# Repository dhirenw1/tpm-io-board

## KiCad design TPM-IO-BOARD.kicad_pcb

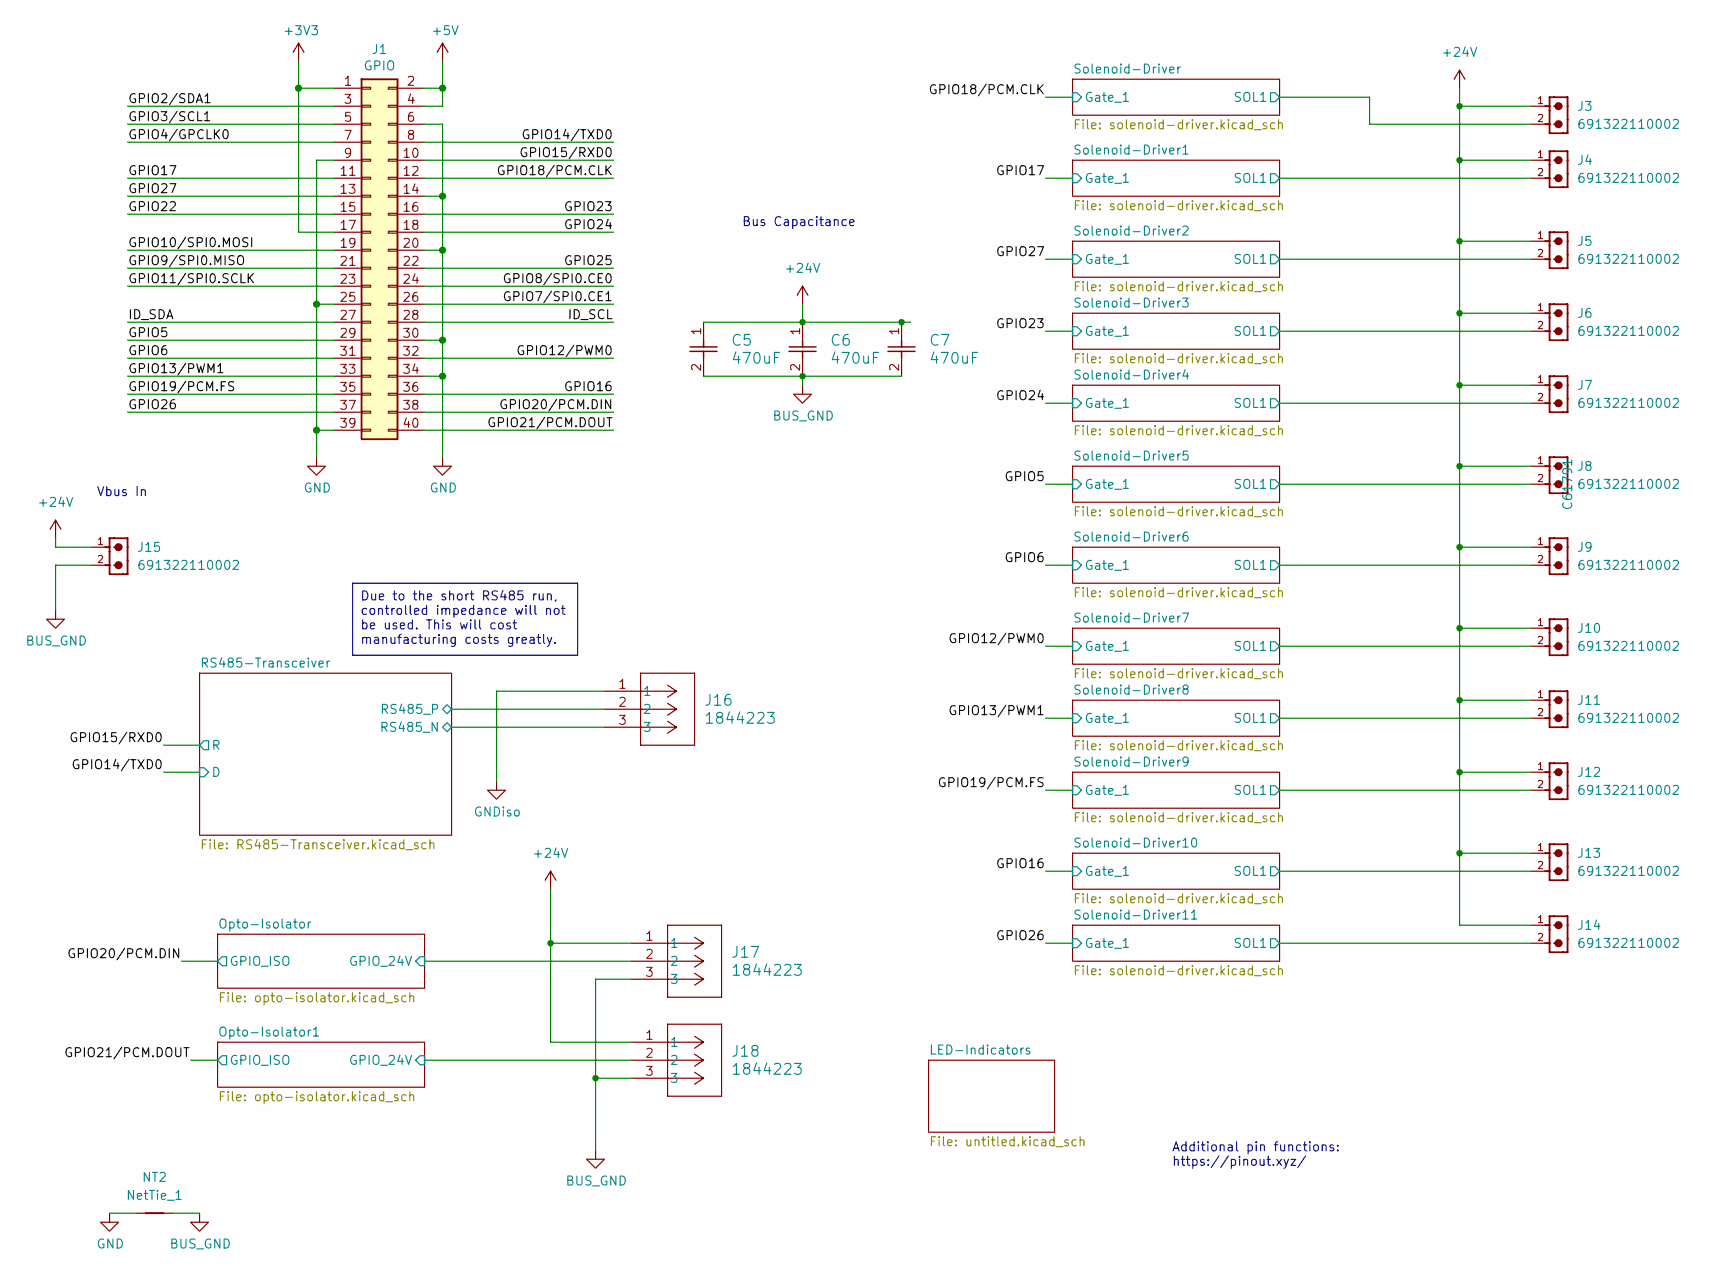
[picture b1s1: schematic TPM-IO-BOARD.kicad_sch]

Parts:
C5, C6, C7: 470uF; CAP_YX_10X16_RUB; LCSC C338196
J1: GPIO; PinSocket_2x20_P2.54mm_Vertical; LCSC C35165
J3, J4, J5, J6, J7, J8, J9, J10, J11, J12, J13, J14, J15: 691322110002; PART-NUMBER 691322110002; LCSC C61791
J16, J17, J18: 1844223; CONN_1844223_PXC; LCSC C5244104
NT2: NetTie_1; NetTie-2_SMD_Pad0.5mm

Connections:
+3V3: J1.1, J1.17; also elsewhere on the board
+5V: J1.2, J1.4; also elsewhere on the board
+24V: C5.1, C6.1, C7.1, J3.1, J4.1, J5.1, J6.1, J7.1, J8.1, J9.1, J10.1, J11.1, J12.1, J13.1, J14.1, J15.1, J17.1, J18.1; also elsewhere on the board
/GPIO2/SDA1: J1.3
/GPIO3/SCL1: J1.5
/GPIO4/GPCLK0: J1.7
/GPIO5: J1.29; also elsewhere on the board
/GPIO6: J1.31; also elsewhere on the board
/GPIO7/SPI0.CE1: J1.26
/GPIO8/SPI0.CE0: J1.24
/GPIO9/SPI0.MISO: J1.21
/GPIO10/SPI0.MOSI: J1.19
/GPIO11/SPI0.SCLK: J1.23
/GPIO12/PWM0: J1.32; also elsewhere on the board
/GPIO13/PWM1: J1.33; also elsewhere on the board
/GPIO14/TXD0: J1.8; also elsewhere on the board
/GPIO15/RXD0: J1.10; also elsewhere on the board
/GPIO16: J1.36; also elsewhere on the board
/GPIO17: J1.11; also elsewhere on the board
/GPIO18/PCM.CLK: J1.12; also elsewhere on the board
/GPIO19/PCM.FS: J1.35; also elsewhere on the board
/GPIO20/PCM.DIN: J1.38; also elsewhere on the board
/GPIO21/PCM.DOUT: J1.40; also elsewhere on the board
/GPIO22: J1.15
/GPIO23: J1.16; also elsewhere on the board
/GPIO24: J1.18; also elsewhere on the board
/GPIO25: J1.22
/GPIO26: J1.37; also elsewhere on the board
/GPIO27: J1.13; also elsewhere on the board
/ID_SCL: J1.28
/ID_SDA: J1.27
/Opto-Isolator1/GPIO_24V: J18.2; also elsewhere on the board
/Opto-Isolator/GPIO_24V: J17.2; also elsewhere on the board
/RS485-Transceiver/RS485_N: J16.3; also elsewhere on the board
/RS485-Transceiver/RS485_P: J16.2; also elsewhere on the board
/Solenoid-Driver1/SOL1: J4.2; also elsewhere on the board
/Solenoid-Driver2/SOL1: J5.2; also elsewhere on the board
/Solenoid-Driver3/SOL1: J6.2; also elsewhere on the board
/Solenoid-Driver4/SOL1: J7.2; also elsewhere on the board
/Solenoid-Driver5/SOL1: J8.2; also elsewhere on the board
/Solenoid-Driver6/SOL1: J9.2; also elsewhere on the board
/Solenoid-Driver7/SOL1: J10.2; also elsewhere on the board
/Solenoid-Driver8/SOL1: J11.2; also elsewhere on the board
/Solenoid-Driver9/SOL1: J12.2; also elsewhere on the board
/Solenoid-Driver10/SOL1: J13.2; also elsewhere on the board
/Solenoid-Driver11/SOL1: J14.2; also elsewhere on the board
/Solenoid-Driver/SOL1: J3.2; also elsewhere on the board
BUS_GND: C5.2, C6.2, C7.2, J15.2, J17.3, J18.3, NT2.2; also elsewhere on the board
GND: J1.6, J1.9, J1.14, J1.20, J1.25, J1.30, J1.34, J1.39, NT2.1; also elsewhere on the board
GNDiso: J16.1; also elsewhere on the board

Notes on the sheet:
Due to the short RS485 run, controlled impedance will not be used. This will cost manufacturing costs greatly.
Additional pin functions: https://pinout.xyz/
Bus Capacitance
Vbus In

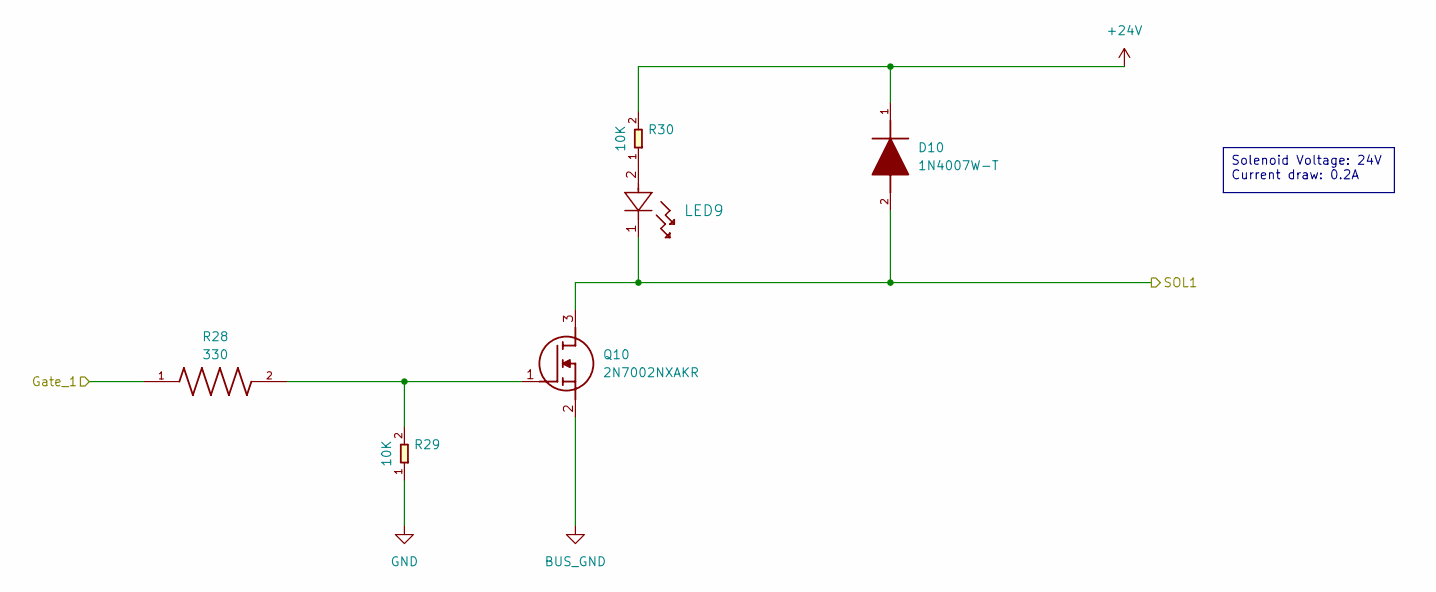
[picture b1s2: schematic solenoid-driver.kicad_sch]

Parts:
D10: 1N4007W-T; SODFL3818X130N; Mouser_Part_Number 583-1N4007W-T
LED9: 5988A10107F; LED_5988A10107F_DIA; LCSC C264407
Q10: 2N7002NXAKR; SOT95P230X110-3N; Mouser Part Number 771-2N7002NXAKR
R28: 330; RESC1005X40N; LCSC C517531
R29, R30: SMD-RES-10K-5_-1__0402_; R0402; MPN RC0402JR-0710KL; LCSC C319934

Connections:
+24V: D10.1, R30.2; also elsewhere on the board
/GPIO19/PCM.FS: R28.1; also elsewhere on the board
/Solenoid-Driver9/SOL1: D10.2, LED9.1, Q10.3 (D); also elsewhere on the board
BUS_GND: Q10.2 (S); also elsewhere on the board
GND: R29.1; also elsewhere on the board
unnamed: LED9.2, R30.1
unnamed: Q10.1 (G), R28.2, R29.2

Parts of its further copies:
D1, D2, D3, D4, D5, D6, D7, D8, D9, D11, D12: 1N4007W-T; SODFL3818X130N; Mouser_Part_Number 583-1N4007W-T
LED1, LED2, LED3, LED4, LED5, LED6, LED7, LED8, LED10, LED11, LED13: 5988A10107F; LED_5988A10107F_DIA; LCSC C264407
Q1, Q2, Q3, Q4, Q5, Q6, Q7, Q8, Q9, Q11, Q12: 2N7002NXAKR; SOT95P230X110-3N; Mouser Part Number 771-2N7002NXAKR
R2, R3, R7, R10, R13, R16, R19, R22, R25, R31, R36: 330; RESC1005X40N; LCSC C517531
R4, R5, R6, R8, R9, R11, R12, R14, R15, R17, R18, R20, R21, R23, R24, R26, R27, R32, R33, R37, R38, R39: SMD-RES-10K-5_-1__0402_; R0402; MPN RC0402JR-0710KL; LCSC C319934

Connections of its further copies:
+24V: D1.1, D2.1, D3.1, D4.1, D5.1, D6.1, D7.1, D8.1, D9.1, D11.1, D12.1, R5.2, R9.2, R12.2, R15.2, R18.2, R21.2, R24.2, R27.2, R33.2, R38.2, R39.2; also elsewhere on the board
/GPIO5: R16.1; also elsewhere on the board
/GPIO6: R19.1; also elsewhere on the board
/GPIO12/PWM0: R22.1; also elsewhere on the board
/GPIO13/PWM1: R25.1; also elsewhere on the board
/GPIO16: R31.1; also elsewhere on the board
/GPIO17: R3.1; also elsewhere on the board
/GPIO18/PCM.CLK: R2.1; also elsewhere on the board
/GPIO23: R10.1; also elsewhere on the board
/GPIO24: R13.1; also elsewhere on the board
/GPIO26: R36.1; also elsewhere on the board
/GPIO27: R7.1; also elsewhere on the board
/Solenoid-Driver1/SOL1: D2.2, LED1.1, Q2.3 (D); also elsewhere on the board
/Solenoid-Driver2/SOL1: D3.2, LED2.1, Q3.3 (D); also elsewhere on the board
/Solenoid-Driver3/SOL1: D4.2, LED3.1, Q4.3 (D); also elsewhere on the board
/Solenoid-Driver4/SOL1: D5.2, LED4.1, Q5.3 (D); also elsewhere on the board
/Solenoid-Driver5/SOL1: D6.2, LED5.1, Q6.3 (D); also elsewhere on the board
/Solenoid-Driver6/SOL1: D7.2, LED6.1, Q7.3 (D); also elsewhere on the board
/Solenoid-Driver7/SOL1: D8.2, LED7.1, Q8.3 (D); also elsewhere on the board
/Solenoid-Driver8/SOL1: D9.2, LED8.1, Q9.3 (D); also elsewhere on the board
/Solenoid-Driver10/SOL1: D11.2, LED10.1, Q11.3 (D); also elsewhere on the board
/Solenoid-Driver11/SOL1: D12.2, LED11.1, Q12.3 (D); also elsewhere on the board
/Solenoid-Driver/SOL1: D1.2, LED13.1, Q1.3 (D); also elsewhere on the board
BUS_GND: Q1.2 (S), Q2.2 (S), Q3.2 (S), Q4.2 (S), Q5.2 (S), Q6.2 (S), Q7.2 (S), Q8.2 (S), Q9.2 (S), Q11.2 (S), Q12.2 (S); also elsewhere on the board
GND: R4.1, R6.1, R8.1, R11.1, R14.1, R17.1, R20.1, R23.1, R26.1, R32.1, R37.1; also elsewhere on the board
unnamed: LED1.2, R5.1
unnamed: LED2.2, R9.1
unnamed: LED3.2, R12.1
unnamed: LED4.2, R15.1
unnamed: LED5.2, R18.1
unnamed: LED6.2, R21.1
unnamed: LED7.2, R24.1
unnamed: LED8.2, R27.1
unnamed: LED10.2, R33.1
unnamed: LED11.2, R39.1
unnamed: LED13.2, R38.1
unnamed: Q1.1 (G), R2.2, R6.2
unnamed: Q2.1 (G), R3.2, R4.2
unnamed: Q3.1 (G), R7.2, R8.2
unnamed: Q4.1 (G), R10.2, R11.2
unnamed: Q5.1 (G), R13.2, R14.2
unnamed: Q6.1 (G), R16.2, R17.2
unnamed: Q7.1 (G), R19.2, R20.2
unnamed: Q8.1 (G), R22.2, R23.2
unnamed: Q9.1 (G), R25.2, R26.2
unnamed: Q11.1 (G), R31.2, R32.2
unnamed: Q12.1 (G), R36.2, R37.2

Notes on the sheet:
Solenoid Voltage: 24V Current draw: 0.2A

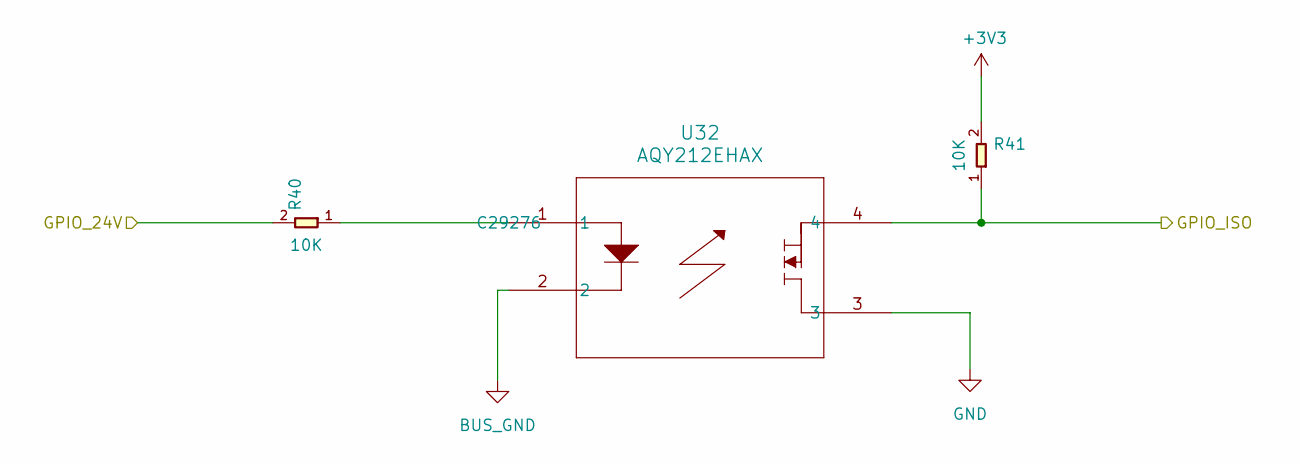
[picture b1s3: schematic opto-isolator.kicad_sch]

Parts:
R40, R41: SMD-RES-10K-5_-1__0402_; R0402; MPN RC0402JR-0710KL; LCSC C319934
U32: AQY212EHAX; RELAY_AQY_SO4_EH_PAN; LCSC C29276

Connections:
+3V3: R41.2; also elsewhere on the board
/GPIO20/PCM.DIN: R41.1, U32.4; also elsewhere on the board
/Opto-Isolator/GPIO_24V: R40.2; also elsewhere on the board
BUS_GND: U32.2; also elsewhere on the board
GND: U32.3; also elsewhere on the board
unnamed: R40.1, U32.1

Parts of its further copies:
R34, R35: SMD-RES-10K-5_-1__0402_; R0402; MPN RC0402JR-0710KL; LCSC C319934
U7: AQY212EHAX; RELAY_AQY_SO4_EH_PAN; LCSC C29276

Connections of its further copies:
+3V3: R35.2; also elsewhere on the board
/GPIO21/PCM.DOUT: R35.1, U7.4; also elsewhere on the board
/Opto-Isolator1/GPIO_24V: R34.2; also elsewhere on the board
BUS_GND: U7.2; also elsewhere on the board
GND: U7.3; also elsewhere on the board
unnamed: R34.1, U7.1

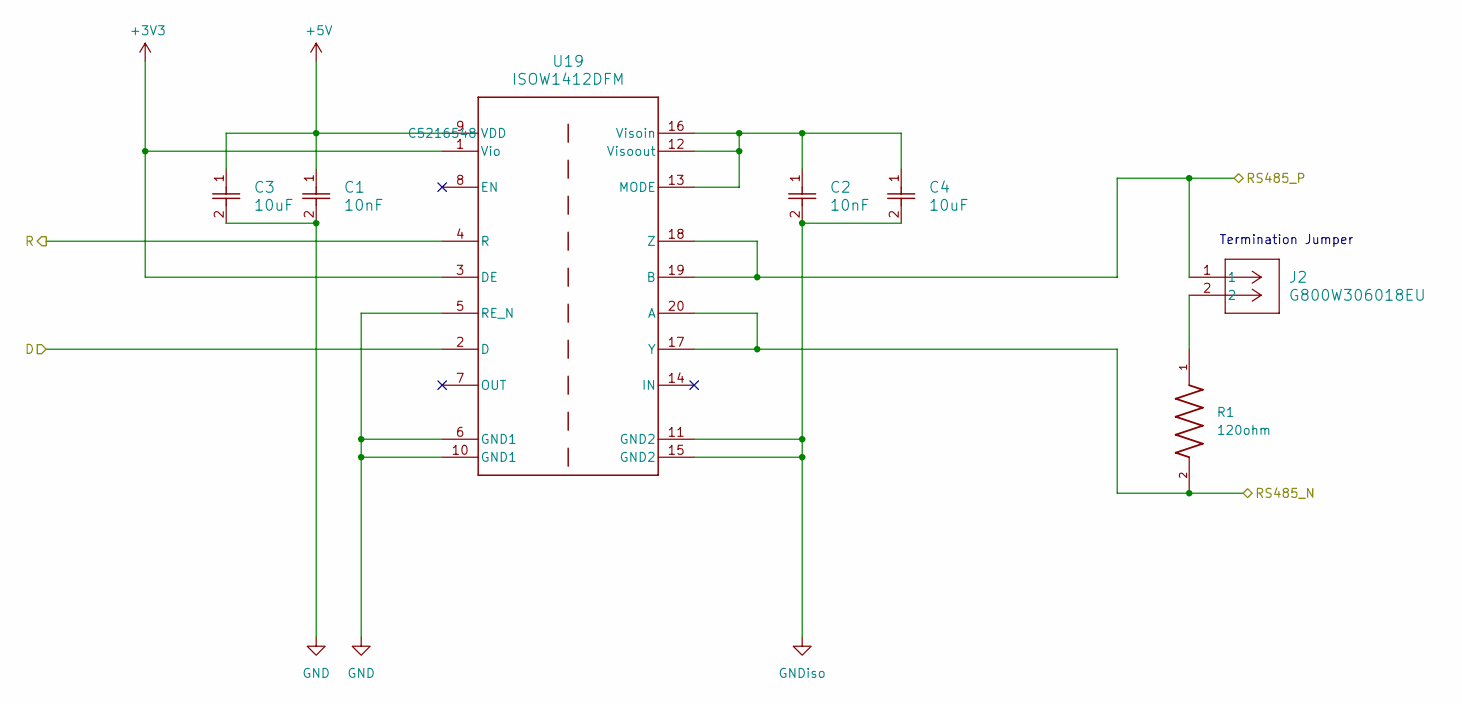
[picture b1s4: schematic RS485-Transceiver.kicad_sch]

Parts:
C1, C2: 10nF; CAPC10555_55N_KEM; LCSC C650944
C3, C4: 10uF; CAP_GRM155R61A106ME11_MUR; LCSC C408132
J2: G800W306018EU; CONN02_G800_5P08X2P5_AMP; LCSC C5360898
R1: 120ohm; RES_ERJPA2F1200X; PARTREV 3/1/2020; LCSC C102779
U19: ISOW1412DFM; DFM0020A-IPC_A; LCSC C5216548

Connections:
+3V3: U19.1 (Vio), U19.3 (DE); also elsewhere on the board
+5V: C1.1, C3.1, U19.9 (VDD); also elsewhere on the board
/GPIO14/TXD0: U19.2 (D); also elsewhere on the board
/GPIO15/RXD0: U19.4 (R); also elsewhere on the board
/RS485-Transceiver/RS485_N: R1.2, U19.17 (Y), U19.20 (A); also elsewhere on the board
/RS485-Transceiver/RS485_P: J2.1, U19.18 (Z), U19.19 (B); also elsewhere on the board
GND: C1.2, C3.2, U19.5 (RE_N), U19.6 (GND1), U19.10 (GND1); also elsewhere on the board
GNDiso: C2.2, C4.2, U19.11 (GND2), U19.15 (GND2); also elsewhere on the board
unnamed: J2.2, R1.1
unnamed: C2.1, C4.1, U19.12 (Visoout), U19.13 (MODE), U19.16 (Visoin)

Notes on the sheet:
Termination Jumper

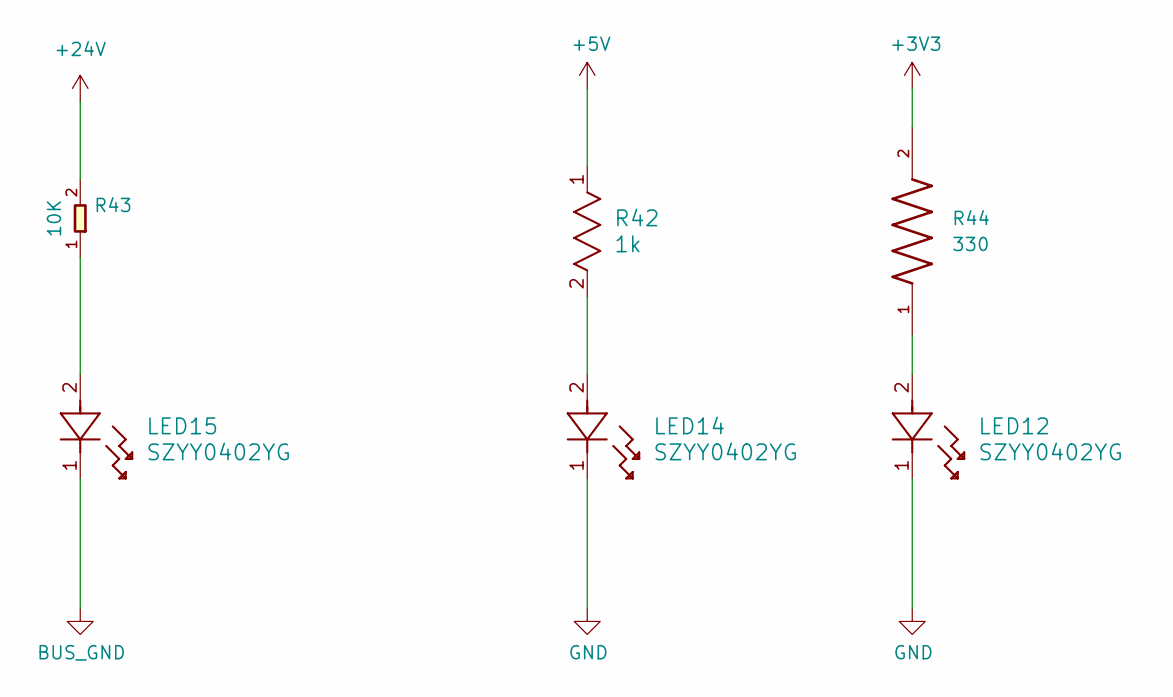
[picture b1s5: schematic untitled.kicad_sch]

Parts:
LED12, LED14, LED15: SZYY0402YG; LED_S73240_WRE; LCSC C434449
R42: 1k; RC0402N_YAG; LCSC C105637
R43: SMD-RES-10K-5_-1__0402_; R0402; MPN RC0402JR-0710KL; LCSC C319934
R44: 330; RESC1005X40N; LCSC C517531

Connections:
+3V3: R44.2; also elsewhere on the board
+5V: R42.1; also elsewhere on the board
+24V: R43.2; also elsewhere on the board
BUS_GND: LED15.1; also elsewhere on the board
GND: LED12.1, LED14.1; also elsewhere on the board
unnamed: LED12.2, R44.1
unnamed: LED14.2, R42.2
unnamed: LED15.2, R43.1

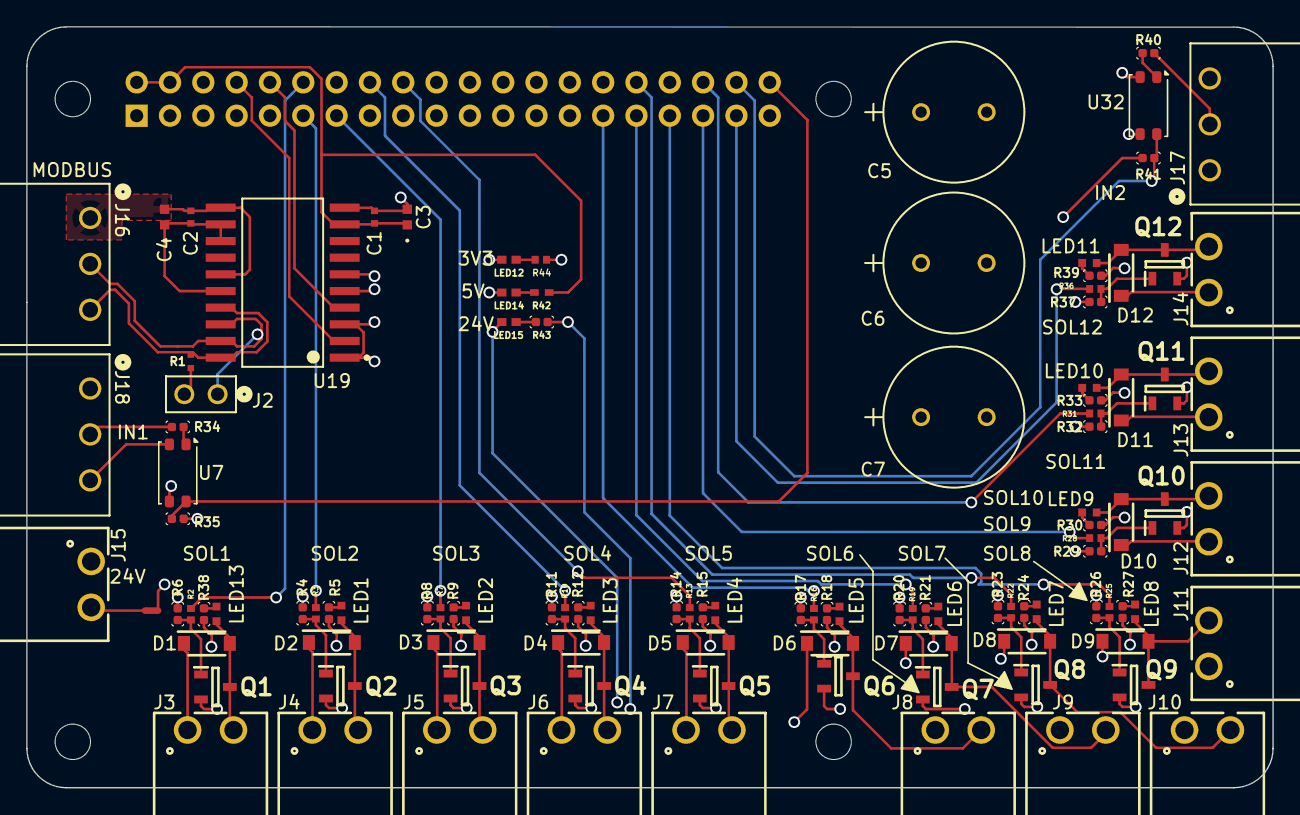
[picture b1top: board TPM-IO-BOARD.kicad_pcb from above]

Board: 4 copper layers, 95.0 x 58.0 mm, 116 parts (1 on the bottom side), 69 nets.

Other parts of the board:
MH1, MH2, MH3, MH4: MountingHole_2.7mm_M2.5

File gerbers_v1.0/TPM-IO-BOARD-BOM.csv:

References,Value,Footprint,LCSC,Quantity
"C1, C2",10nF,CAPC10555_55N_KEM,C650944,2
"C3, C4",10uF,CAP_GRM155R61A106ME11_MUR,C408132,2
C5,470uF,CAP_YX_10X16_RUB,C338196,1
"R4, R5, R6, R8, R9, R11, R12, R14, R15, R17, R18, R20, R21, R23, R24, R26, R27, R29, R30, R32, R33, R34, R35, R37, R38, R39, R40, R41, R43",SMD-RES-10K-5_-1__0402_,R0402,C319934,29
"R2, R3, R7, R10, R13, R16, R19, R22, R25, R28, R31, R36, R44",330,RESC1005X40N,C517531,13
R1,120ohm,RES_ERJPA2F1200X,C102779,1
R42,1k,RC0402N_YAG,C105637,1
"D1, D2, D3, D4, D5, D6, D7, D8, D9, D10, D11, D12",1N4007W-T,SODFL3818X130N,C328592,12
"U7, U32",AQY212EHAX,Panasonic_APV-AQY_SSOP-4_4.45x2.65mm_P1.27mm,C29276,2
U19,ISOW1412DFM,DFM0020A-IPC_A,C5216548,1
"LED1, LED2, LED3, LED4, LED5, LED6, LED7, LED8, LED9, LED10, LED11, LED13",5988A10107F,LED_5988A10107F_DIA,C264407,12
"Q1, Q2, Q3, Q4, Q5, Q6, Q7, Q8, Q9, Q10, Q11, Q12",2N7002NXAKR,SOT95P230X110-3N,C414015,12
"LED12, LED14, LED15",SZYY0402YG,LED_S73240_WRE,C434449,3
"J3, J4, J5, J6, J7, J8, J9, J10, J11, J12, J13, J14, J15",6.91E+11,6.91E+11,C61791,13
"J16, J17, J18",1844223,CONN_1844223_PXC,C5244104,3
J1,GPIO,PinSocket_2x20_P2.54mm_Vertical,C35165,1
J2,G800W306018EU,CONN02_G800_5P08X2P5_AMP,C5360898,1

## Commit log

2024-09-01 removed top level directory
2024-09-04 Updating file with shifted GND net tie
2024-09-10 v1.0 ordered
